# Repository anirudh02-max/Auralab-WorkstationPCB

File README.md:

# Auralab-WorkstationPCB
Advanced 4-layer PCB design featuring split-plane noise isolation (AGND/DGND) and asynchronous dual-core processing. Implements a handheld multi-tool oscilloscope, current tracker, and symmetrical DC power supply.

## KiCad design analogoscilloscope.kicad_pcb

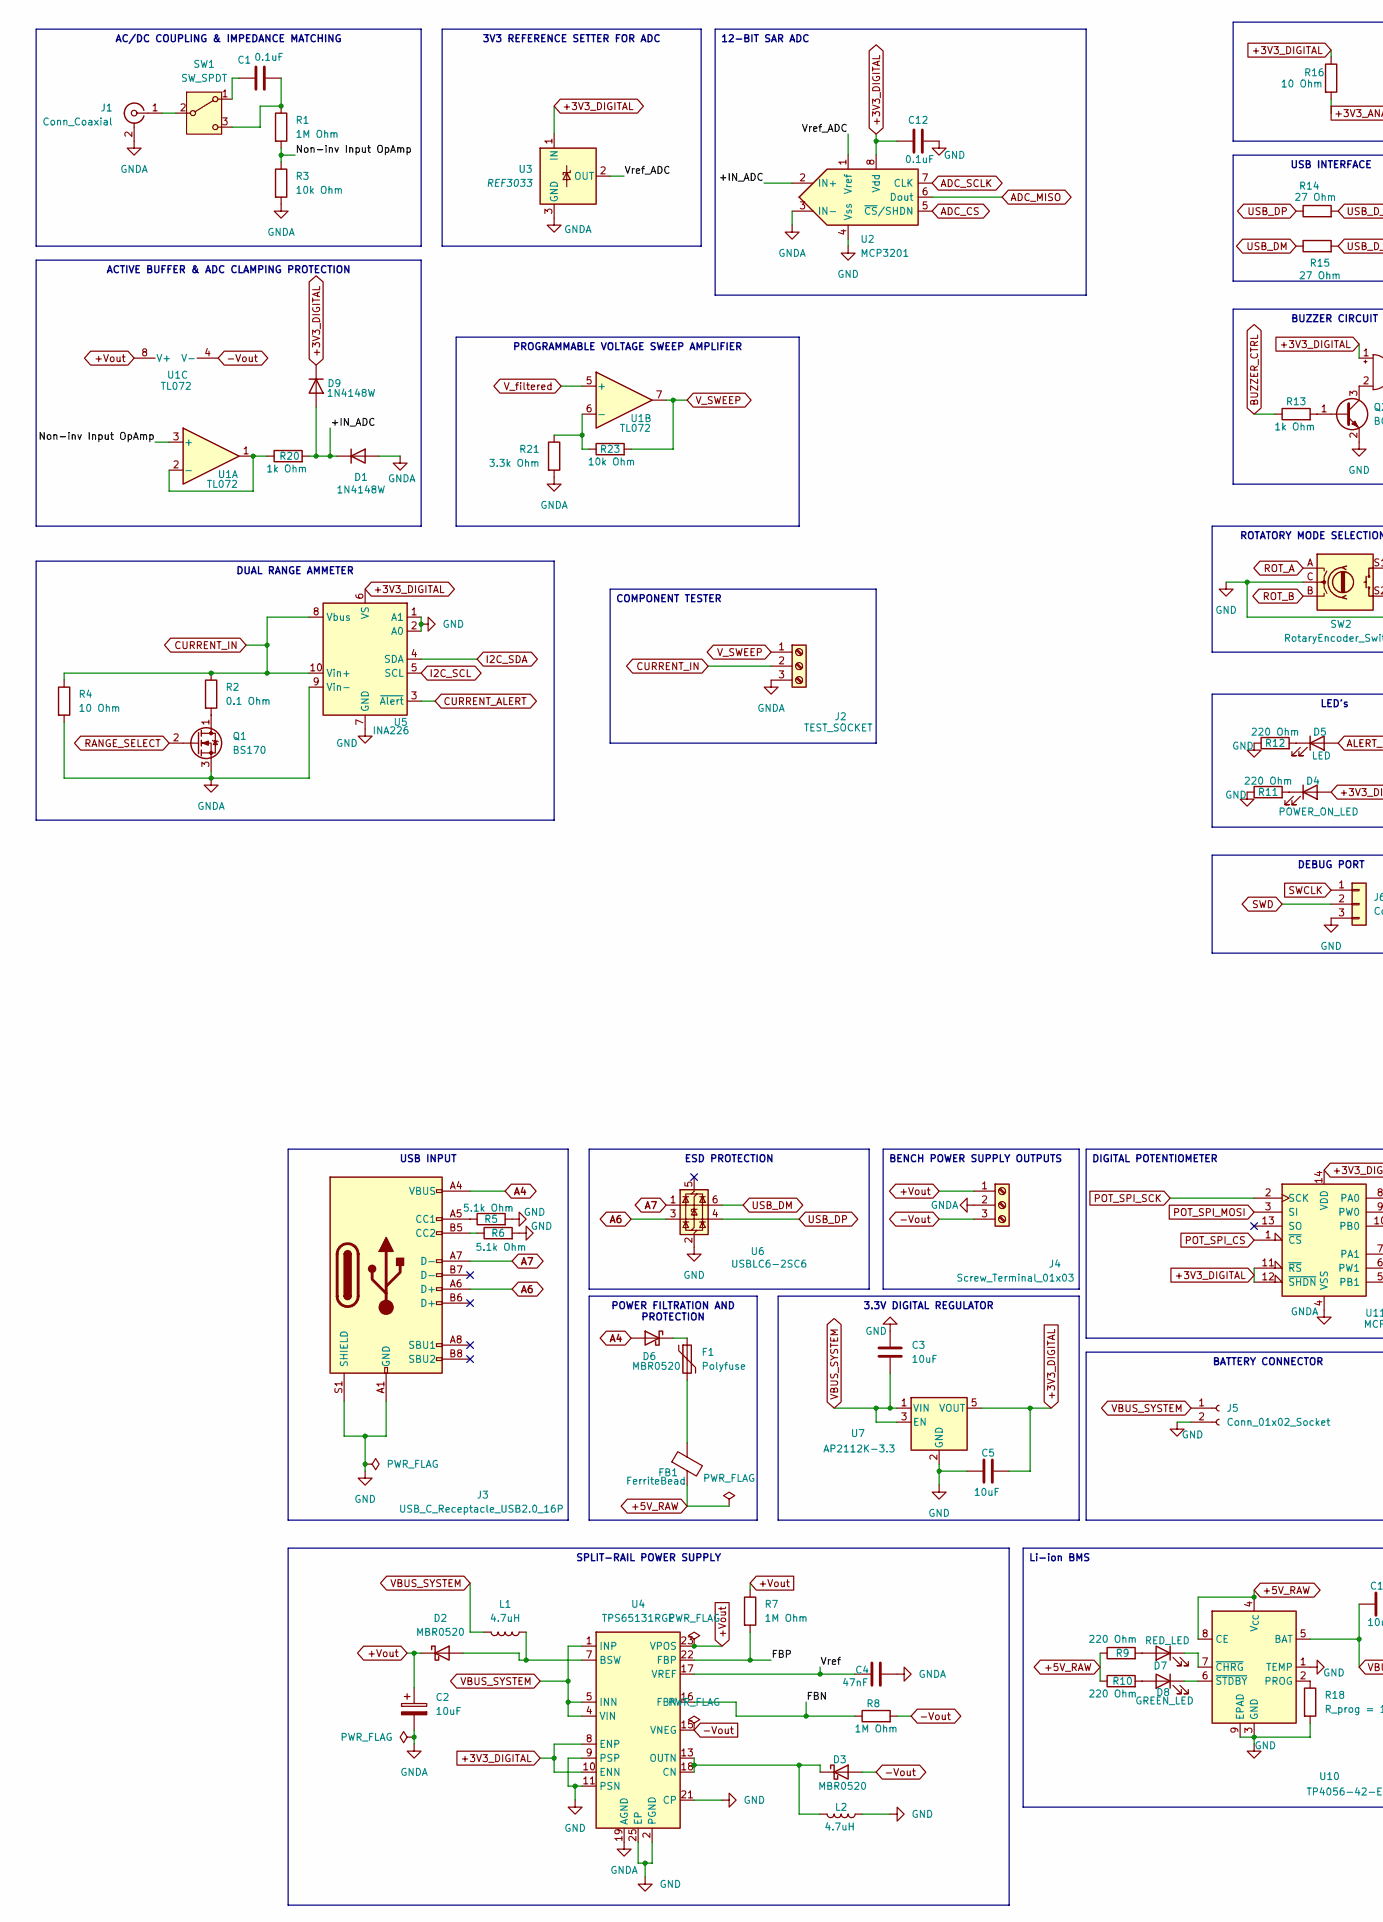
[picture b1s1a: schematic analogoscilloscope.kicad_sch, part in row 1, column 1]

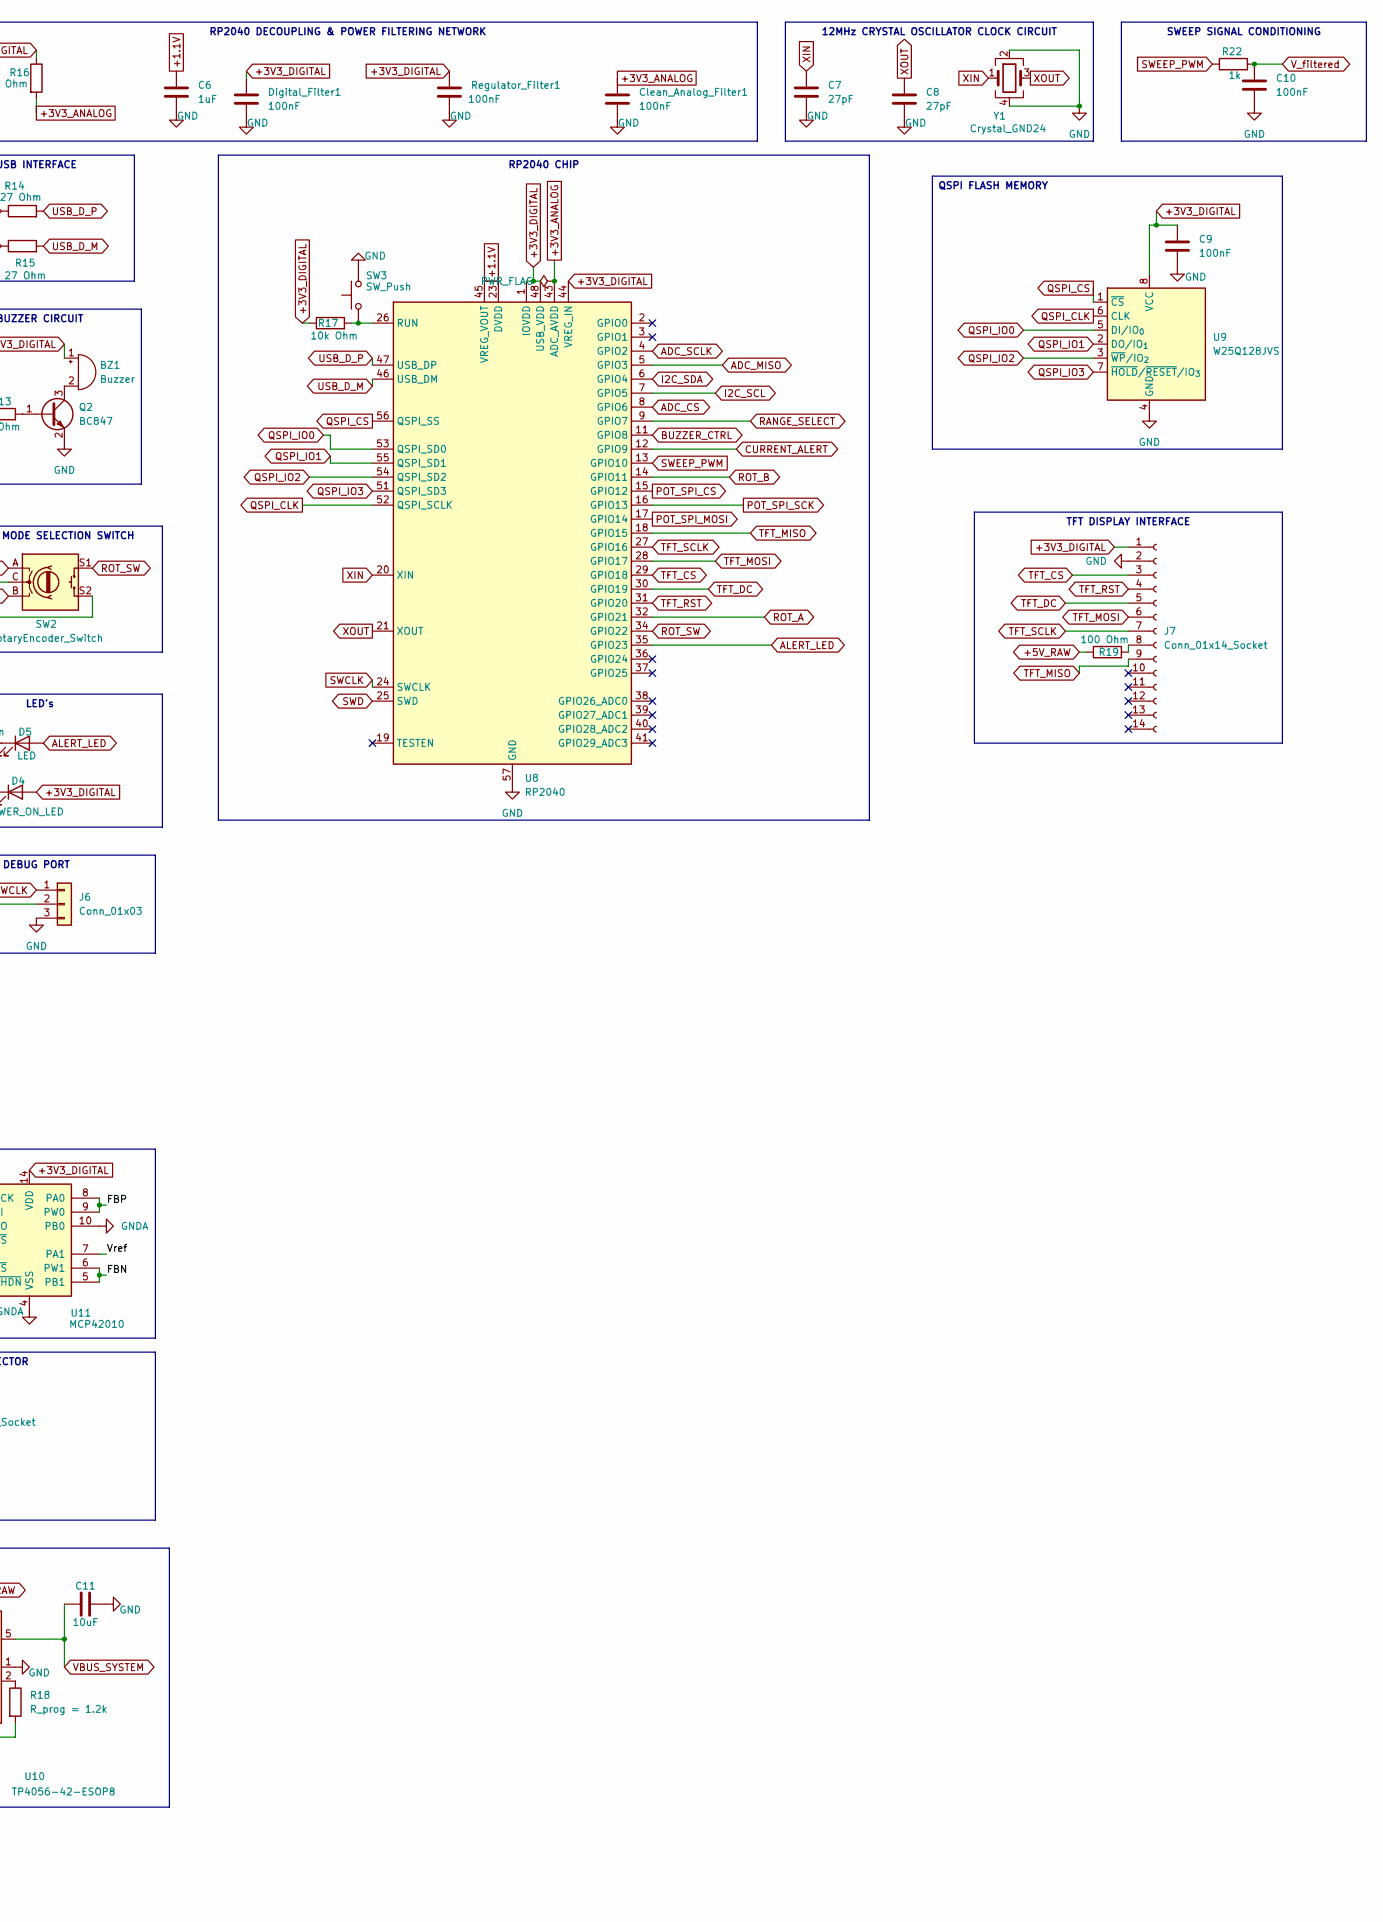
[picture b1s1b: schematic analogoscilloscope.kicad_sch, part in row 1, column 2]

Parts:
BZ1: Buzzer; Buzzer_CUI_CPT-9019S-SMT
C1, C12: 0.1uF; C_0805_2012Metric
C2: 10uF; CP_EIA-6032-28_Kemet-C_HandSolder
C3, C5, C11: 10uF; C_0805_2012Metric_Pad1.18x1.45mm_HandSolder
C4: 47nF; C_0805_2012Metric_Pad1.18x1.45mm_HandSolder
C6: 1uF; C_0805_2012Metric_Pad1.18x1.45mm_HandSolder
C7, C8: 27pF; C_0805_2012Metric_Pad1.18x1.45mm_HandSolder
C9, C10: 100nF; C_0805_2012Metric_Pad1.18x1.45mm_HandSolder
Clean_Analog_Filter1: 100nF; C_0805_2012Metric_Pad1.18x1.45mm_HandSolder
D1, D9: 1N4148W; D_SOD-123
D2, D3, D6: MBR0520; D_SOD-123
D4: POWER_ON_LED; LED_0805_2012Metric_Pad1.15x1.40mm_HandSolder
D5: LED; LED_0805_2012Metric_Pad1.15x1.40mm_HandSolder
D7: RED_LED; LED_0805_2012Metric_Pad1.15x1.40mm_HandSolder
D8: GREEN_LED; LED_0805_2012Metric_Pad1.15x1.40mm_HandSolder
Digital_Filter1: 100nF; C_0805_2012Metric_Pad1.18x1.45mm_HandSolder
F1: Polyfuse; Fuse_1206_3216Metric
FB1: FerriteBead; L_0805_2012Metric
J1: Conn_Coaxial; BNC_Amphenol_B6252HB-NPP3G-50_Horizontal
J2: TEST_SOCKET; TerminalBlock_Phoenix_MPT-0,5-3-2.54_1x03_P2.54mm_Horizontal
J3: USB_C_Receptacle_USB2.0_16P; USB_C_Receptacle_HRO_TYPE-C-31-M-12
J4: Screw_Terminal_01x03; TerminalBlock_MaiXu_MX126-5.0-03P_1x03_P5.00mm
J5: Conn_01x02_Socket; JST_PH_B2B-PH-K_1x02_P2.00mm_Vertical
J6: Conn_01x03; PinHeader_1x03_P2.54mm_Vertical
J7: Conn_01x14_Socket; PinSocket_1x14_P2.54mm_Vertical
L1, L2: 4.7uH; L_6.3x6.3_H3
Q1: BS170; TO-92_Inline
Q2: BC847; SOT-23
R1: 1M Ohm; R_0805_2012Metric
R2: 0.1 Ohm; R_0805_2012Metric
R3, R23: 10k Ohm; R_0805_2012Metric
R4: 10 Ohm; R_0805_2012Metric
R5, R6: 5.1k Ohm; R_0805_2012Metric_Pad1.20x1.40mm_HandSolder
R7, R8: 1M Ohm; R_0805_2012Metric_Pad1.20x1.40mm_HandSolder
R9, R10, R11, R12: 220 Ohm; R_0805_2012Metric_Pad1.20x1.40mm_HandSolder
R13: 1k Ohm; R_0805_2012Metric_Pad1.20x1.40mm_HandSolder
R14, R15: 27 Ohm; R_0805_2012Metric_Pad1.20x1.40mm_HandSolder
R16: 10 Ohm; R_0805_2012Metric_Pad1.20x1.40mm_HandSolder
R17: 10k Ohm; R_0805_2012Metric_Pad1.20x1.40mm_HandSolder
R18: R_prog = 1.2k; R_0805_2012Metric_Pad1.20x1.40mm_HandSolder
R19: 100 Ohm; R_0805_2012Metric_Pad1.20x1.40mm_HandSolder
R20: 1k Ohm; R_0805_2012Metric
R21: 3.3k Ohm; R_0805_2012Metric
R22: 1k; R_0805_2012Metric_Pad1.20x1.40mm_HandSolder
Regulator_Filter1: 100nF; C_0805_2012Metric_Pad1.18x1.45mm_HandSolder
SW1: SW_SPDT; SW_SPDT_PCM12
SW2: RotaryEncoder_Switch; RotaryEncoder_Alps_EC11E-Switch_Vertical_H20mm
SW3: SW_Push; SW_PUSH-12mm_Wuerth-430476085716
U1: TL072; SOIC-8_3.9x4.9mm_P1.27mm
U2: MCP3201; SOIC-8_3.9x4.9mm_P1.27mm
U3: REF3033; SOT-23
U4: TPS65131RGE; VQFN-24-1EP_4x4mm_P0.5mm_EP2.45x2.45mm_ThermalVias
U5: INA226; MSOP-10_3x3mm_P0.5mm
U6: USBLC6-2SC6; SOT-23-6
U7: AP2112K-3.3; SOT-23-5
U8: RP2040; QFN-56-1EP_7x7mm_P0.4mm_EP3.2x3.2mm
U9: W25Q128JVS; SOIC-8_5.3x5.3mm_P1.27mm
U10: TP4056-42-ESOP8; SOIC-8-1EP_3.9x4.9mm_P1.27mm_EP2.41x3.3mm_ThermalVias
U11: MCP42010; SOIC-14_3.9x8.7mm_P1.27mm
Y1: Crystal_GND24; Crystal_SMD_3225-4Pin_3.2x2.5mm_HandSoldering

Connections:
+1.1V: C6.1, U8.23 (DVDD), U8.45 (VREG_VOUT), U8.50 (DVDD)
+3V3_ANALOG: Clean_Analog_Filter1.1, R16.2, U8.43 (ADC_AVDD)
+3V3_DIGITAL: BZ1.1 (+), C5.1, C9.1, C12.1, D4.2 (A), D9.1 (K), Digital_Filter1.1, J7.1, R16.1, R17.1, Regulator_Filter1.1, U2.8 (Vdd), U3.1 (IN), U4.8 (ENP), U4.10 (ENN), U5.6 (VS), U7.5 (VOUT), U8.1 (IOVDD), U8.10 (IOVDD), U8.22 (IOVDD), U8.33 (IOVDD), U8.42 (IOVDD), U8.44 (VREG_IN), U8.48 (USB_VDD), U8.49 (IOVDD), U9.8 (VCC), U11.11 (~RS), U11.12 (~SHDN), U11.14 (VDD)
+5V_RAW: FB1.2, R9.1, R10.1, R19.1, U10.4 (V_{CC}), U10.8 (CE)
+Vout: C2.1, D2.1 (K), J4.1, R7.1, U1.8 (V+), U4.23 (VPOS)
-Vout: D3.2 (A), J4.3, R8.2, U1.4 (V-), U4.15 (VNEG)
/+IN_ADC: D1.1 (K), D9.2 (A), R20.2, U2.2 (IN+)
/FBN: R8.1, U4.16 (FBN), U11.5 (PB1), U11.6 (PW1)
/FBP: R7.2, U4.22 (FBP), U11.8 (PA0), U11.9 (PW0)
/Non-inv Input OpAmp: R1.2, R3.1, U1.3 (+)
/Vref: C4.1, U4.17 (VREF), U11.7 (PA1)
/Vref_ADC: U2.1 (Vref), U3.2 (OUT)
A4: D6.2 (A), J3.A4 (VBUS), J3.A9 (VBUS), J3.B4 (VBUS), J3.B9 (VBUS)
A6: J3.A6 (D+), U6.3 (I/O2)
A7: J3.A7 (D-), U6.1 (I/O1)
ADC_CS: U2.5 (~CS/SHDN), U8.8 (GPIO6)
ADC_MISO: U2.6 (Dout), U8.5 (GPIO3)
ADC_SCLK: U2.7 (CLK), U8.4 (GPIO2)
ALERT_LED: D5.2 (A), U8.35 (GPIO23)
BUZZER_CTRL: R13.1, U8.11 (GPIO8)
CURRENT_ALERT: U5.3 (~Alert), U8.12 (GPIO9)
CURRENT_IN: J2.2, R2.1, R4.1, U5.8 (Vbus), U5.10 (Vin+)
GND: C3.1, C5.2, C6.2, C7.2, C8.2, C9.2, C10.2, C11.2, C12.2, Clean_Analog_Filter1.2, Digital_Filter1.2, J3.A1 (GND), J3.A12 (GND), J3.B1 (GND), J3.B12 (GND), J3.S1 (SHIELD), J5.2, J6.3, J7.2, L2.1, Q2.2 (E), R5.2, R6.2, R11.1, R12.1, R18.2, Regulator_Filter1.2, SW2.C, SW2.S2, SW3.2, U2.4 (Vss), U4.2 (PGND), U4.3 (PGND), U4.9 (PSP), U4.11 (PSN), U4.21 (CP), U4.25 (EP), U5.1 (A1), U5.2 (A0), U5.7 (GND), U6.2 (GND), U7.2 (GND), U8.57 (GND), U9.4 (GND), U10.1 (TEMP), U10.3 (GND), U10.9 (EPAD), Y1.2, Y1.4
GNDA: C2.2, C4.2, D1.2 (A), J1.2 (Ext), J2.3, J4.2, Q1.3 (S), R3.2, R4.2, R21.2, U2.3 (IN-), U3.3 (GND), U4.19 (AGND), U5.9 (Vin-), U11.4 (VSS), U11.10 (PB0)
I2C_SCL: U5.5 (SCL), U8.7 (GPIO5)
I2C_SDA: U5.4 (SDA), U8.6 (GPIO4)
unnamed: BZ1.2 (-), Q2.3 (C)
unnamed: D2.2 (A), L1.1, U4.7 (BSW)
unnamed: D3.1 (K), L2.2, U4.13 (OUTN), U4.14 (OUTN), U4.18 (CN)
unnamed: D4.1 (K), R11.2
unnamed: D5.1 (K), R12.2
unnamed: D6.1 (K), F1.1
unnamed: D7.2 (A), R9.2
unnamed: D7.1 (K), U10.7 (~CHRG)
unnamed: D8.2 (A), R10.2
unnamed: D8.1 (K), U10.6 (~STDBY)
unnamed: F1.2, FB1.1
unnamed: J1.1 (In), SW1.2 (B)
unnamed: J3.A5 (CC1), R5.1
unnamed: J3.B5 (CC2), R6.1
unnamed: J7.8, R19.2
unnamed: Q1.1 (D), R2.2
unnamed: Q2.1 (B), R13.2
unnamed: C1.1, SW1.1 (A)
unnamed: C1.2, R1.1, SW1.3 (C)
unnamed: R20.1, U1.1, U1.2 (-)
unnamed: R21.1, R23.1, U1.6 (-)
unnamed: R17.2, SW3.1, U8.26 (RUN)
unnamed: R18.1, U10.2 (PROG)
POT_SPI_CS: U8.15 (GPIO12), U11.1 (~CS)
POT_SPI_MOSI: U8.17 (GPIO14), U11.3 (SI)
POT_SPI_SCK: U8.16 (GPIO13), U11.2 (SCK)
QSPI_CLK: U8.52 (QSPI_SCLK), U9.6 (CLK)
QSPI_CS: U8.56 (QSPI_SS), U9.1 (~CS)
QSPI_IO0: U8.53 (QSPI_SD0), U9.5 (DI/IO_{0})
QSPI_IO1: U8.55 (QSPI_SD1), U9.2 (DO/IO_{1})
QSPI_IO2: U8.54 (QSPI_SD2), U9.3 (~WP/IO_{2})
QSPI_IO3: U8.51 (QSPI_SD3), U9.7 (~HOLD/~RESET/IO_{3})
RANGE_SELECT: Q1.2 (G), U8.9 (GPIO7)
ROT_A: SW2.A, U8.32 (GPIO21)
ROT_B: SW2.B, U8.14 (GPIO11)
ROT_SW: SW2.S1, U8.34 (GPIO22)
SWCLK: J6.1, U8.24 (SWCLK)
SWD: J6.2, U8.25 (SWD)
SWEEP_PWM: R22.1, U8.13 (GPIO10)
TFT_CS: J7.3, U8.29 (GPIO18)
TFT_DC: J7.5, U8.30 (GPIO19)
TFT_MISO: J7.9, U8.18 (GPIO15)
TFT_MOSI: J7.6, U8.28 (GPIO17)
TFT_RST: J7.4, U8.31 (GPIO20)
TFT_SCLK: J7.7, U8.27 (GPIO16)
USB_DM: R15.1, U6.6 (I/O1)
USB_DP: R14.1, U6.4 (I/O2)
USB_D_M: R15.2, U8.46 (USB_DM)
USB_D_P: R14.2, U8.47 (USB_DP)
VBUS_SYSTEM: C3.2, C11.1, J5.1, L1.2, U4.1 (INP), U4.4 (VIN), U4.5 (INN), U4.6 (INN), U4.24 (INP), U7.1 (VIN), U7.3 (EN), U10.5 (BAT)
V_SWEEP: J2.1, R23.2, U1.7
V_filtered: C10.1, R22.2, U1.5 (+)
XIN: C7.1, U8.20 (XIN), Y1.1
XOUT: C8.1, U8.21 (XOUT), Y1.3

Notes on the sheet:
USB INPUT
PROGRAMMABLE VOLTAGE SWEEP AMPLIFIER
BENCH POWER SUPPLY OUTPUTS
BUZZER CIRCUIT
COMPONENT TESTER
QSPI FLASH MEMORY
BATTERY CONNECTOR
POWER FILTRATION AND PROTECTION
RP2040 CHIP
3V3 REFERENCE SETTER FOR ADC
LED's
SWEEP SIGNAL CONDITIONING
ESD PROTECTION
SPLIT-RAIL POWER SUPPLY
AC/DC COUPLING & IMPEDANCE MATCHING
12-BIT SAR ADC
DEBUG PORT
3.3V DIGITAL REGULATOR
12MHz CRYSTAL OSCILLATOR CLOCK CIRCUIT
RP2040 DECOUPLING & POWER FILTERING NETWORK
ROTATORY MODE SELECTION SWITCH
USB INTERFACE
DUAL RANGE AMMETER
ACTIVE BUFFER & ADC CLAMPING PROTECTION
DIGITAL POTENTIOMETER
Li-ion BMS
TFT DISPLAY INTERFACE

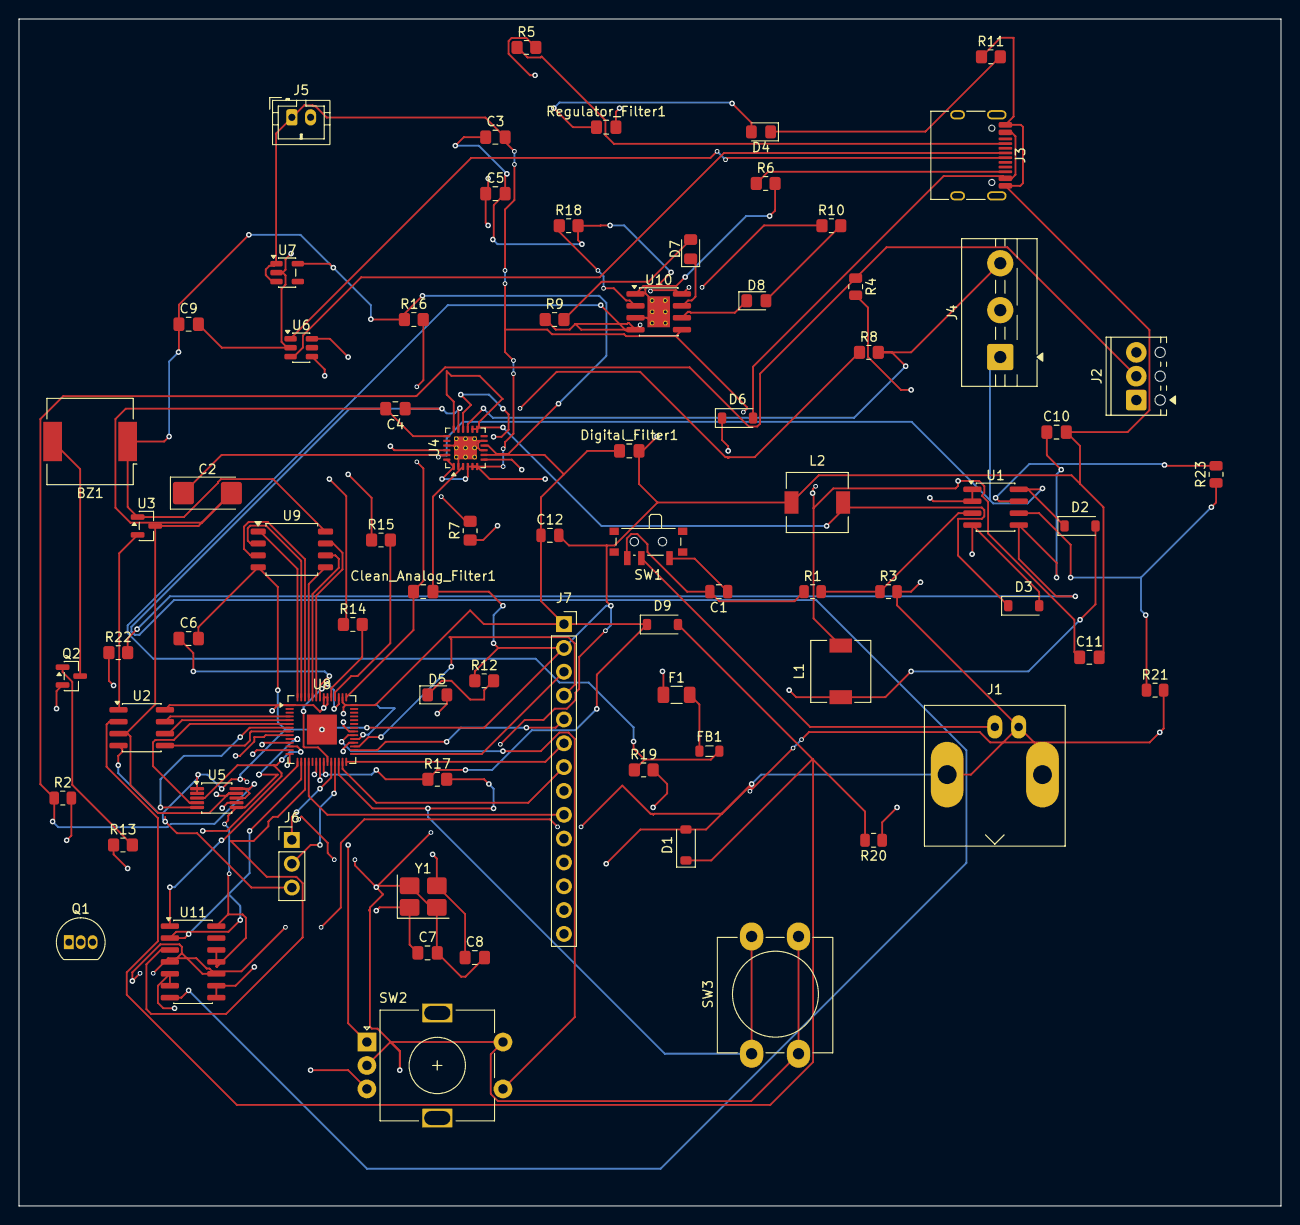
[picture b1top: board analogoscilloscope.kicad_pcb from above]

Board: 4 copper layers, 134.5 x 126.5 mm, 76 parts (0 on the bottom side), 80 nets.
